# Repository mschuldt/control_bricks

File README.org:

Control Bricks

A collection of composable PCBs for building simple automation solutions.

Bricks are connected in sequence, each performing a simple function before
passing control to the next brick. 
Bricks can have sensor inputs, and outputs for actuators.

The goal is to create reliable and maintainable solutions 
without any custom application specific software. 
The PCBs provide buttons and indicators for the control interface. 
Each output has buttons for manual activation for testing and debugging.

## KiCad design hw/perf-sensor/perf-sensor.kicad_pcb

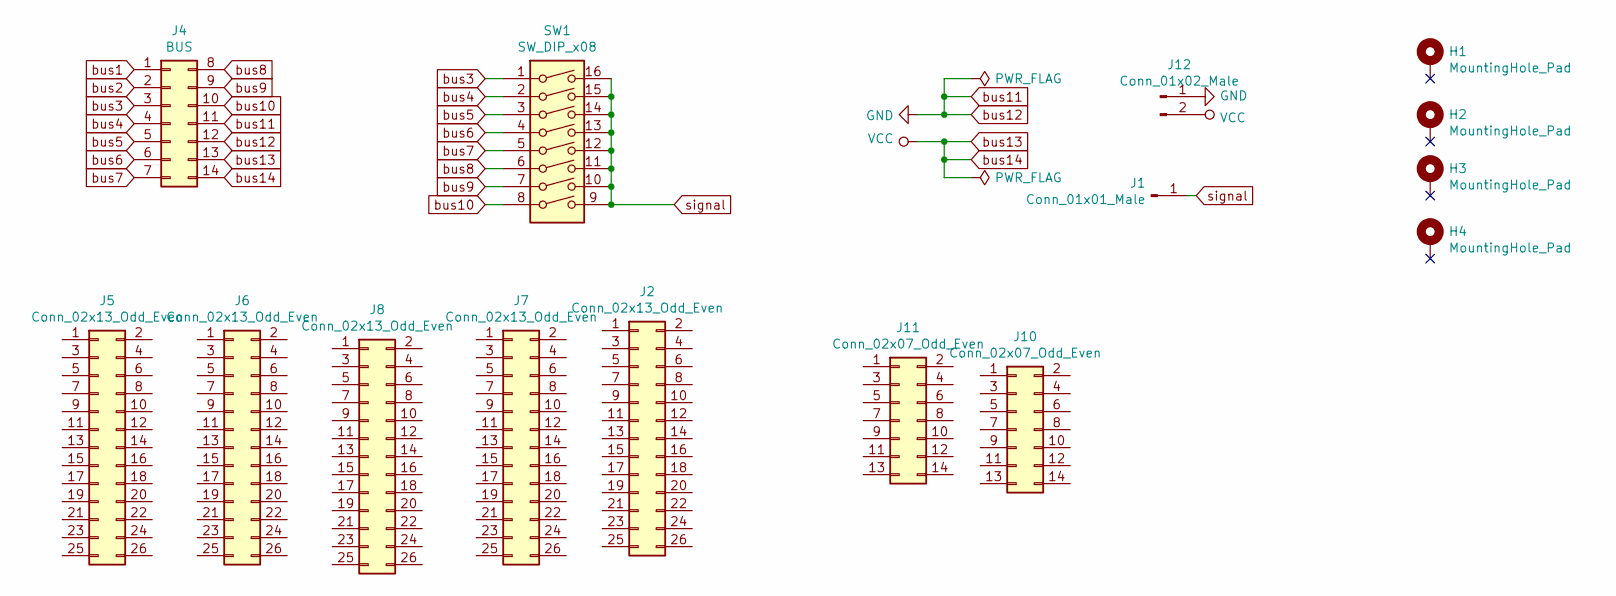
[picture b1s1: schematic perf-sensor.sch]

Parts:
H1, H2, H3, H4: MountingHole_Pad; MountingHole_3.2mm_M3
J1: Conn_01x01_Male; PinHeader_1x01_P2.54mm_Vertical
J2, J5, J6, J7, J8: Conn_02x13_Odd_Even; PinHeader_2x13_P2.54mm_Vertical
J4: BUS; PinHeader_2x07_P2.54mm_Vertical
J10, J11: Conn_02x07_Odd_Even; PinHeader_2x07_P2.54mm_Vertical
J12: Conn_01x02_Male; PinHeader_1x02_P2.54mm_Vertical
SW1: SW_DIP_x08; DIP-16_W7.62mm_SMDSocket_SmallPads

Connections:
bus1: J4.1
bus2: J4.2
bus3: J4.3, SW1.1
bus4: J4.4, SW1.2
bus5: J4.5, SW1.3
bus6: J4.6, SW1.4
bus7: J4.7, SW1.5
bus8: J4.8, SW1.6
bus9: J4.9, SW1.7
bus10: J4.10, SW1.8
bus11: J4.11, J4.12, J12.1
bus13: J4.13, J4.14, J12.2
signal: J1.1, SW1.9, SW1.10, SW1.11, SW1.12, SW1.13, SW1.14, SW1.15, SW1.16

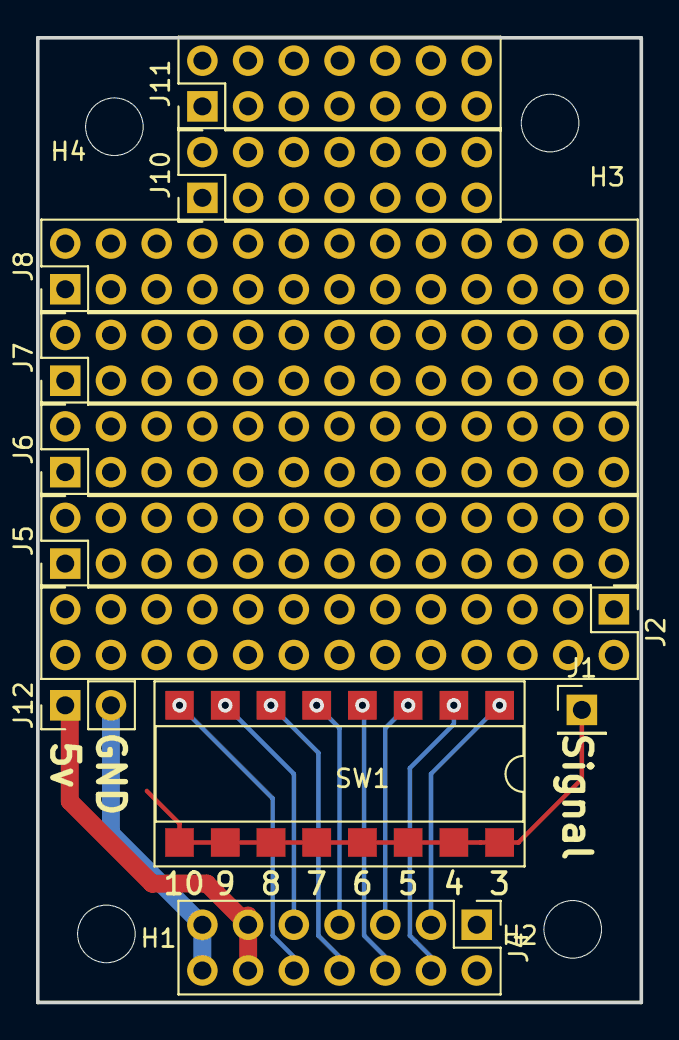
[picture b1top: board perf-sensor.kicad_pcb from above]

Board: 2 copper layers, 33.5 x 53.6 mm, 15 parts (0 on the bottom side), 11 nets.

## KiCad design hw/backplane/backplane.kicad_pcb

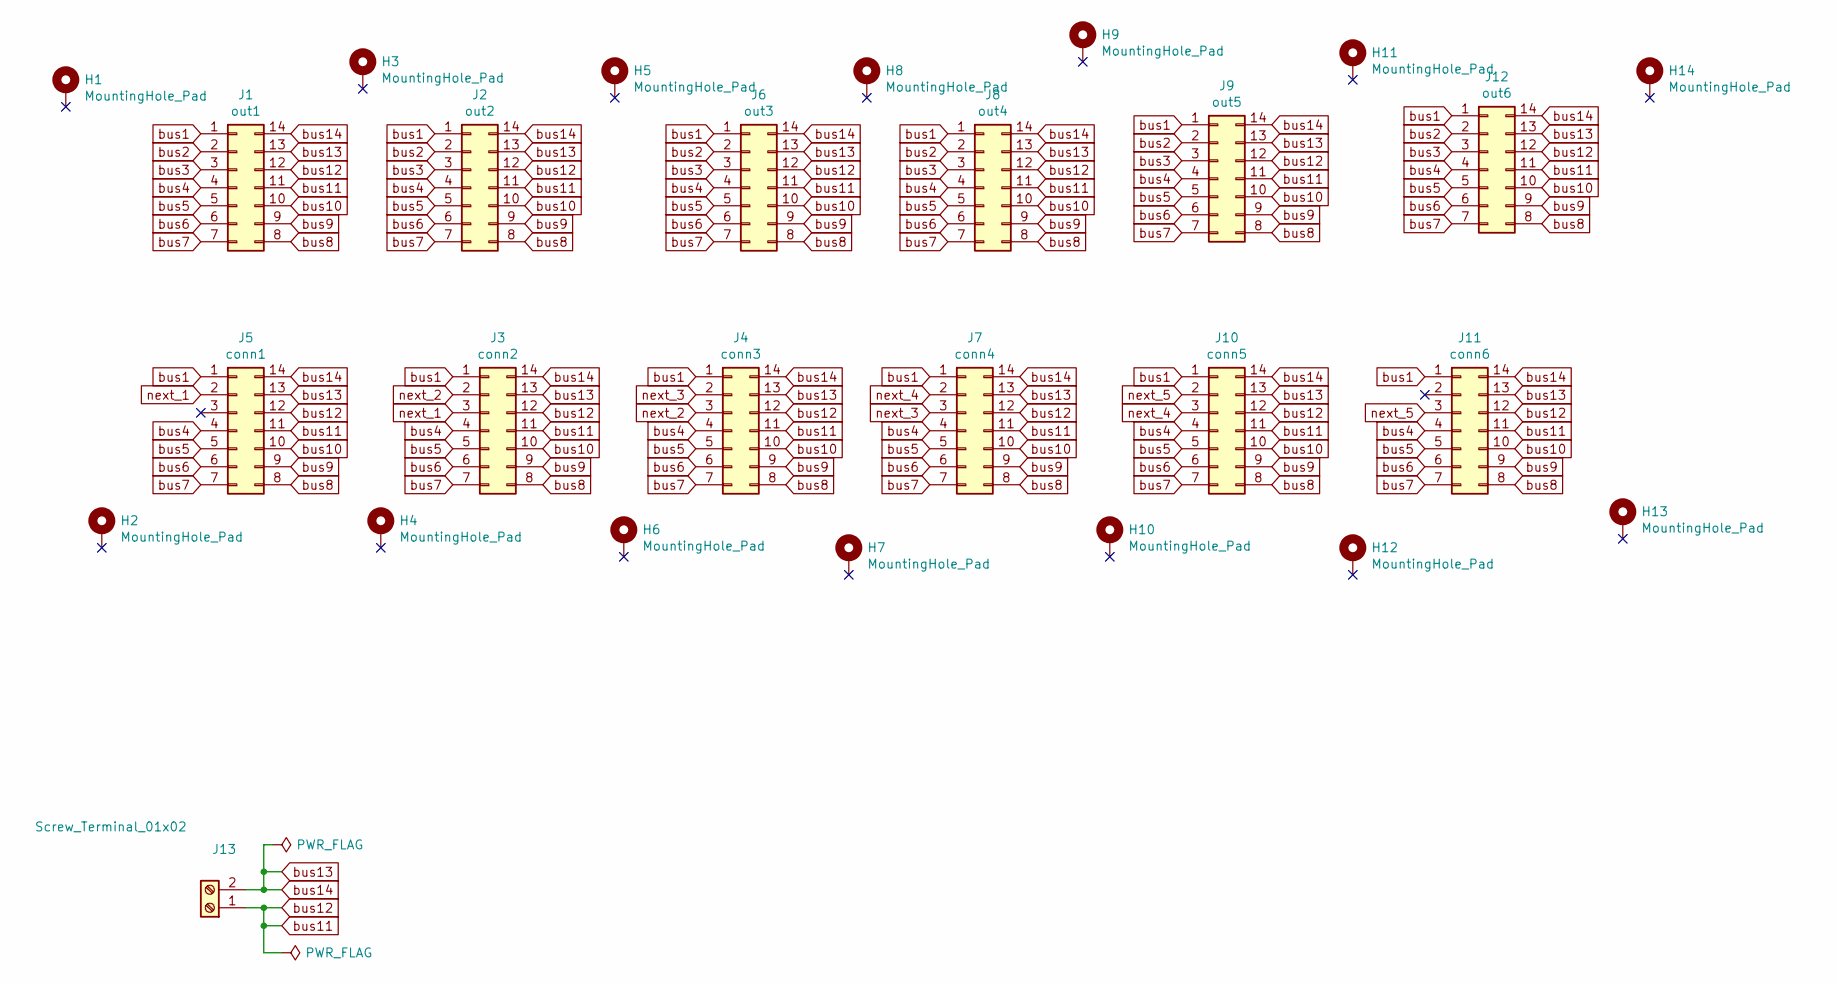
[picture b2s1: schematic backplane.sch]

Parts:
H1, H2, H3, H4, H5, H6, H7, H8, H9, H10, H11, H12, H13, H14: MountingHole_Pad; MountingHole_3.2mm_M3_Pad
J1: out1; PinHeader_2x07_P2.54mm_Vertical
J2: out2; PinHeader_2x07_P2.54mm_Vertical
J3: conn2; PinHeader_2x07_P2.54mm_Vertical
J4: conn3; PinHeader_2x07_P2.54mm_Vertical
J5: conn1; PinHeader_2x07_P2.54mm_Vertical
J6: out3; PinHeader_2x07_P2.54mm_Vertical
J7: conn4; PinHeader_2x07_P2.54mm_Vertical
J8: out4; PinHeader_2x07_P2.54mm_Vertical
J9: out5; PinHeader_2x07_P2.54mm_Vertical
J10: conn5; PinHeader_2x07_P2.54mm_Vertical
J11: conn6; PinHeader_2x07_P2.54mm_Vertical
J12: out6; PinHeader_2x07_P2.54mm_Vertical
J13: Screw_Terminal_01x02; PinHeader_1x02_P2.54mm_Vertical

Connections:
bus1: J1.1, J2.1, J3.1, J4.1, J5.1, J6.1, J7.1, J8.1, J9.1, J10.1, J11.1, J12.1
bus2: J1.2, J2.2, J6.2, J8.2, J9.2, J12.2
bus3: J1.3, J2.3, J6.3, J8.3, J9.3, J12.3
bus4: J1.4, J2.4, J3.4, J4.4, J5.4, J6.4, J7.4, J8.4, J9.4, J10.4, J11.4, J12.4
bus5: J1.5, J2.5, J3.5, J4.5, J5.5, J6.5, J7.5, J8.5, J9.5, J10.5, J11.5, J12.5
bus6: J1.6, J2.6, J3.6, J4.6, J5.6, J6.6, J7.6, J8.6, J9.6, J10.6, J11.6, J12.6
bus7: J1.7, J2.7, J3.7, J4.7, J5.7, J6.7, J7.7, J8.7, J9.7, J10.7, J11.7, J12.7
bus8: J1.8, J2.8, J3.8, J4.8, J5.8, J6.8, J7.8, J8.8, J9.8, J10.8, J11.8, J12.8
bus9: J1.9, J2.9, J3.9, J4.9, J5.9, J6.9, J7.9, J8.9, J9.9, J10.9, J11.9, J12.9
bus10: J1.10, J2.10, J3.10, J4.10, J5.10, J6.10, J7.10, J8.10, J9.10, J10.10, J11.10, J12.10
bus11: J1.11, J1.12, J2.11, J2.12, J3.11, J3.12, J4.11, J4.12, J5.11, J5.12, J6.11, J6.12, J7.11, J7.12, J8.11, J8.12, J9.11, J9.12, J10.11, J10.12, J11.11, J11.12, J12.11, J12.12, J13.1
bus13: J1.13, J1.14, J2.13, J2.14, J3.13, J3.14, J4.13, J4.14, J5.13, J5.14, J6.13, J6.14, J7.13, J7.14, J8.13, J8.14, J9.13, J9.14, J10.13, J10.14, J11.13, J11.14, J12.13, J12.14, J13.2
next_1: J3.3, J5.2
next_2: J3.2, J4.3
next_3: J4.2, J7.3
next_4: J7.2, J10.3
next_5: J10.2, J11.3

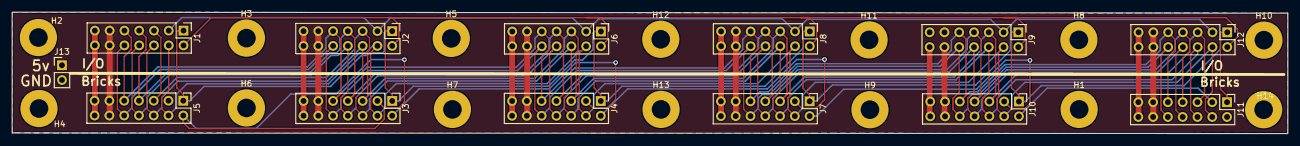
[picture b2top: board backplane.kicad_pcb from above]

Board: 2 copper layers, 219.2 x 20.9 mm, 27 parts (0 on the bottom side), 17 nets.

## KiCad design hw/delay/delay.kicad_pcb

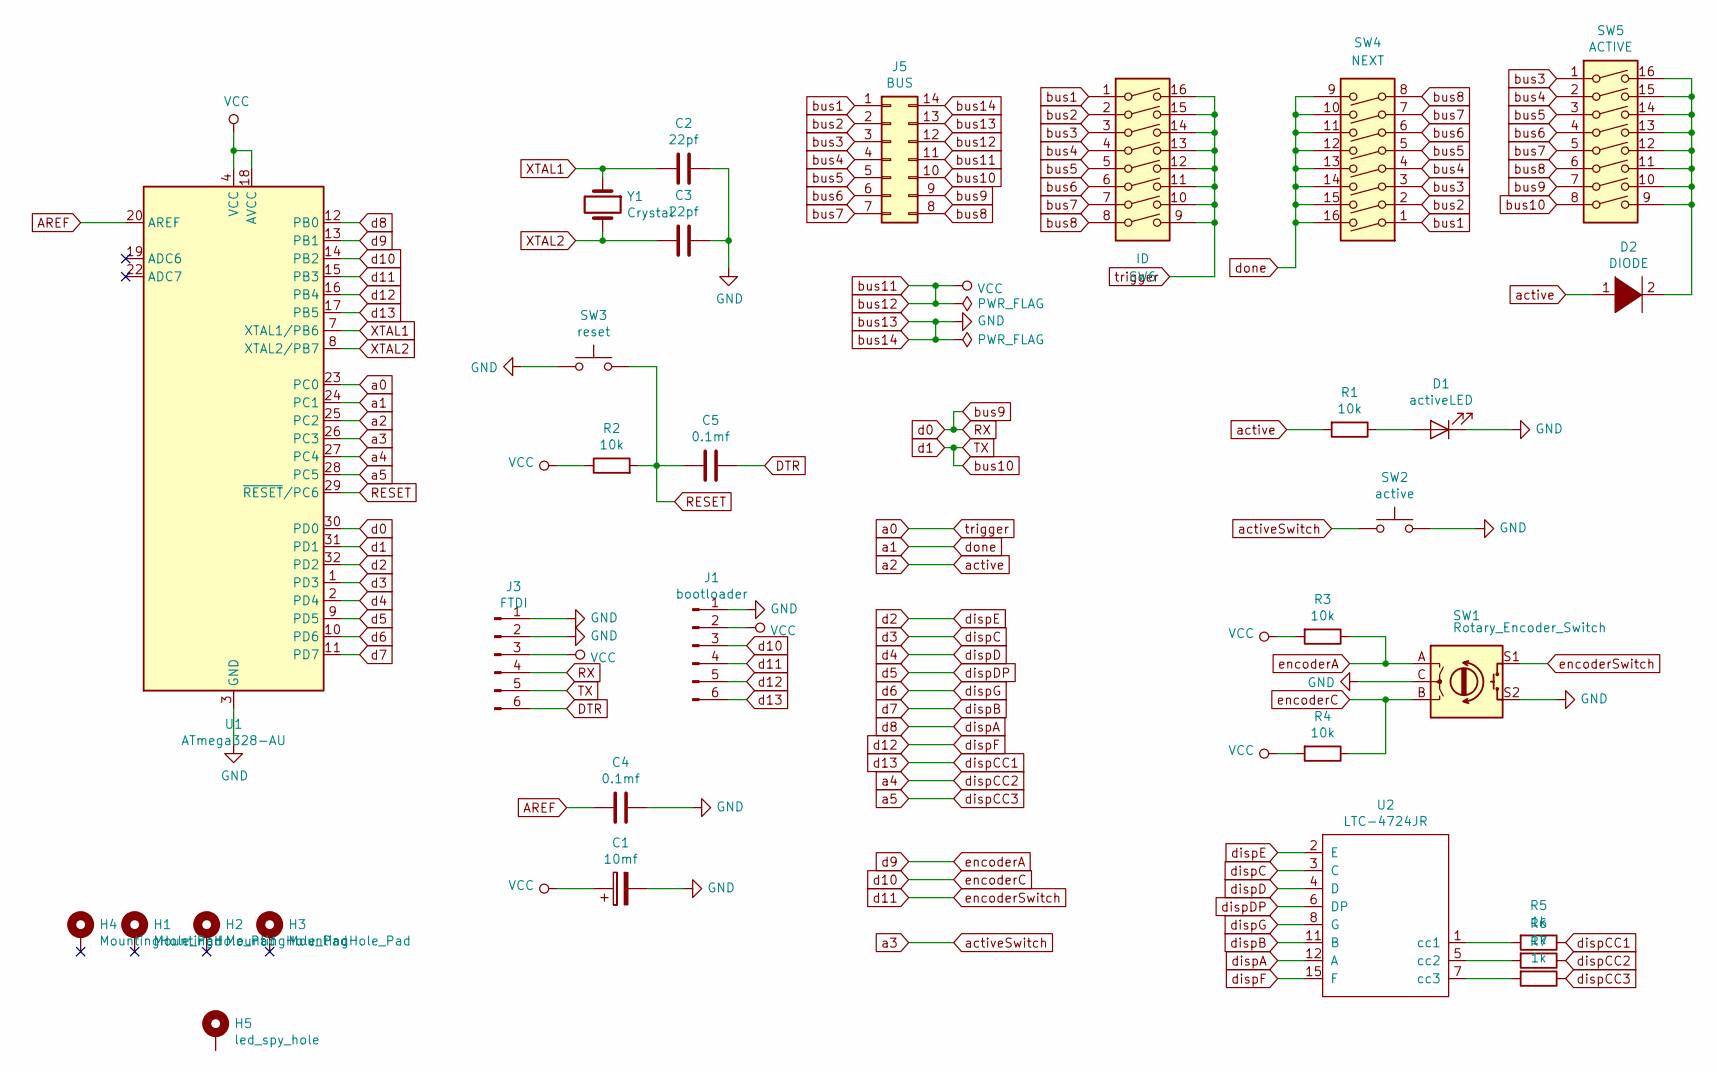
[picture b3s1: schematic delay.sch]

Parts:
C1: 10mf; C_0603_1608Metric
C2, C3: 22pf; C_0603_1608Metric
C4, C5: 0.1mf; C_0603_1608Metric
D1: activeLED; LED_D5.0mm
D2: DIODE; D_0603_1608Metric
H1, H2, H3, H4: MountingHole_Pad; MountingHole_3.2mm_M3_Pad
H5: led_spy_hole; MountingHole_3.2mm_M3
J1: bootloader; edge_connector_3
J3: FTDI; edge_connector_3
J5: BUS; PinHeader_2x07_P2.54mm_Vertical
R1, R2, R3, R4: 10k; R_0603_1608Metric
R5, R6, R7: 1k; R_0603_1608Metric
SW1: Rotary_Encoder_Switch; RotaryEncoder_Alps_EC11E-Switch_Vertical_H20mm_CircularMoun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
SW2: active; SW_SPST_TL3305C
SW3: reset; SW_SPST_TL3305C
SW4: NEXT; DIP-16_W7.62mm_SMDSocket_SmallPads
SW5: ACTIVE; DIP-16_W7.62mm_SMDSocket_SmallPads
SW6: ID; DIP-16_W7.62mm_SMDSocket_SmallPads
U1: ATmega328-AU; TQFP-32_7x7mm_P0.8mm
U2: LTC-4724JR
Y1: Crystal; Crystal_SMD_HC49-SD

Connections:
AREF: C4.1, U1.20 (AREF)
DTR: C5.2, J3.6
unnamed: D1.2 (A), R1.1
unnamed: D2.2 (A), SW5.9, SW5.10, SW5.11, SW5.12, SW5.13, SW5.14, SW5.15, SW5.16
unnamed: R5.2, U2.1 (cc1)
unnamed: R6.2, U2.5 (cc2)
unnamed: R7.2, U2.7 (cc3)
RESET: C5.1, R2.2, SW3.2, U1.29 (~RESET~/PC6)
RX: J3.4, J5.9, SW5.7, U1.30 (PD0)
TX: J3.5, J5.10, SW5.8, U1.31 (PD1)
XTAL1: C2.2, U1.7 (XTAL1/PB6), Y1.1
XTAL2: C3.2, U1.8 (XTAL2/PB7), Y1.2
a0: SW6.9, SW6.10, SW6.11, SW6.12, SW6.13, SW6.14, SW6.15, SW6.16, U1.23 (PC0)
a1: SW4.9, SW4.10, SW4.11, SW4.12, SW4.13, SW4.14, SW4.15, SW4.16, U1.24 (PC1)
a2: D2.1 (K), R1.2, U1.25 (PC2)
a3: SW2.1, U1.26 (PC3)
a4: R6.1, U1.27 (PC4)
a5: R7.1, U1.28 (PC5)
bus1: J5.1, SW4.1, SW6.1
bus2: J5.2, SW4.2, SW6.2
bus3: J5.3, SW4.3, SW5.1, SW6.3
bus4: J5.4, SW4.4, SW5.2, SW6.4
bus5: J5.5, SW4.5, SW5.3, SW6.5
bus6: J5.6, SW4.6, SW5.4, SW6.6
bus7: J5.7, SW4.7, SW5.5, SW6.7
bus8: J5.8, SW4.8, SW5.6, SW6.8
bus11: C1.1, J1.2, J3.3, J5.11, J5.12, R2.1, R3.2, R4.2, U1.4 (VCC), U1.6 (VCC), U1.18 (AVCC)
bus13: C1.2, C2.1, C3.1, C4.2, D1.1 (K), J1.1, J3.1, J3.2, J5.13, J5.14, SW1.C, SW1.S2, SW2.2, SW3.1, U1.3 (GND), U1.5 (GND), U1.21 (GND)
d2: U1.32 (PD2), U2.2 (E)
d3: U1.1 (PD3), U2.3 (C)
d4: U1.2 (PD4), U2.4 (D)
d5: U1.9 (PD5), U2.6 (DP)
d6: U1.10 (PD6), U2.8 (G)
d7: U1.11 (PD7), U2.11 (B)
d8: U1.12 (PB0), U2.12 (A)
d9: R3.1, SW1.A, U1.13 (PB1)
d10: J1.3, R4.1, SW1.B, U1.14 (PB2)
d11: J1.4, SW1.S1, U1.15 (PB3)
d12: J1.5, U1.16 (PB4), U2.15 (F)
d13: J1.6, R5.1, U1.17 (PB5)

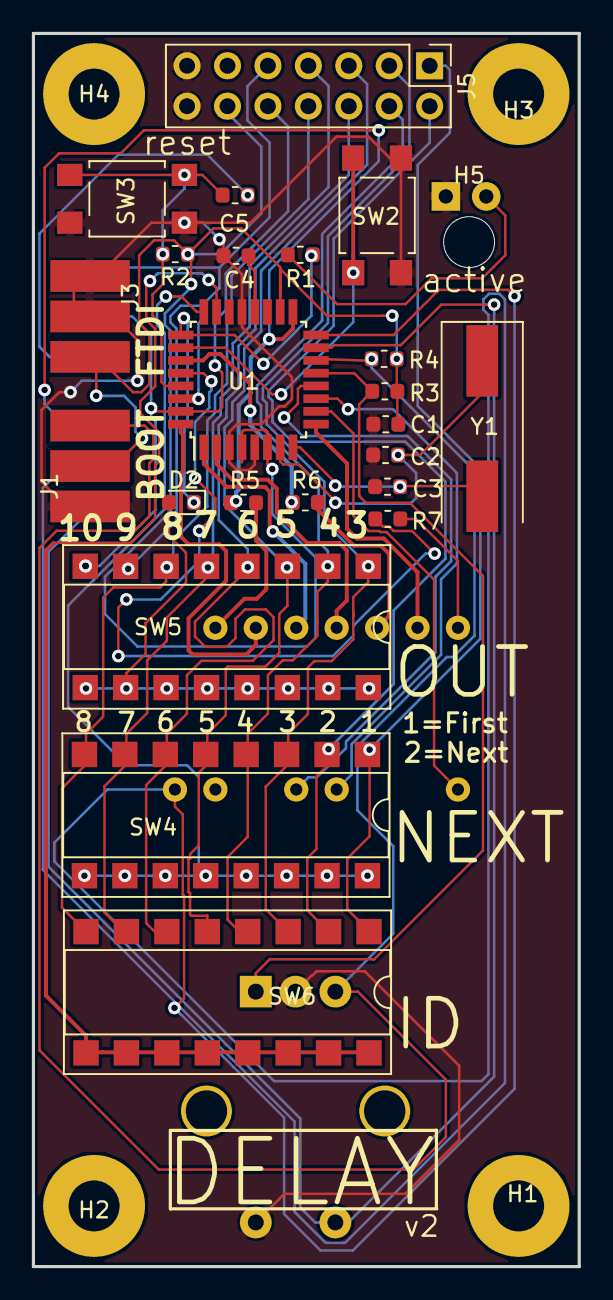
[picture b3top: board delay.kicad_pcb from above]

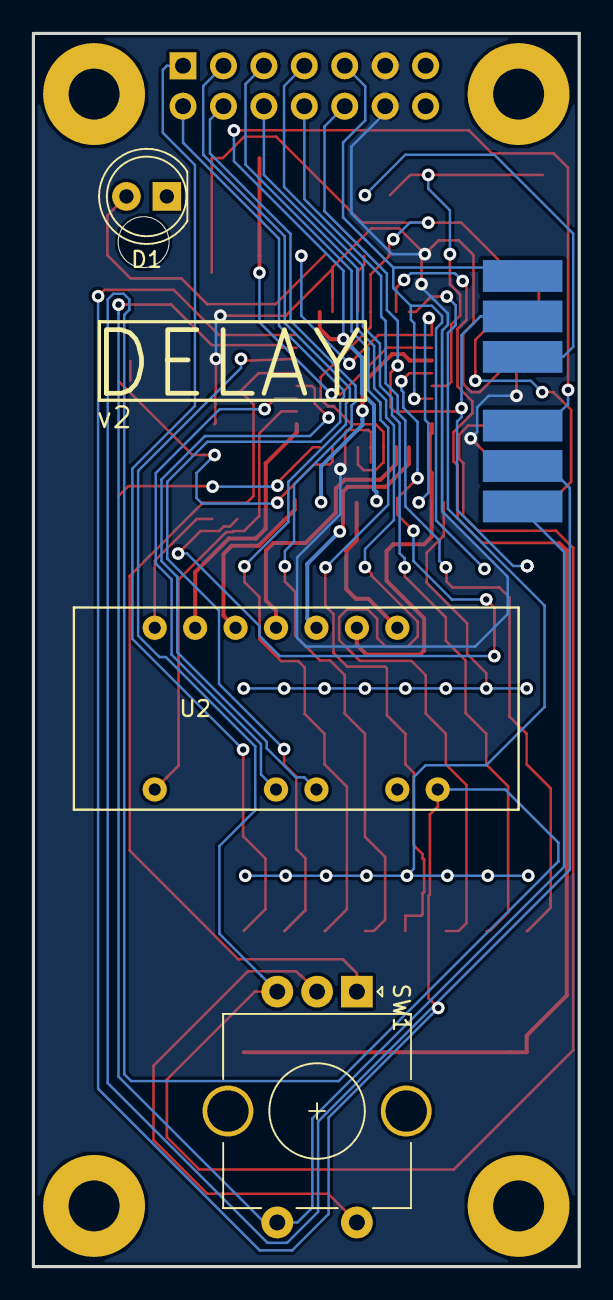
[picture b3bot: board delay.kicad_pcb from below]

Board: 2 copper layers, 34.3 x 77.5 mm, 31 parts (3 on the bottom side), 40 nets.

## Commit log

2018-11-02 initial
2018-11-02 update hardware
2018-11-21 DELAY block v2
2018-11-21 WHILE block v2
2018-11-21 COUNT block v2
2018-11-21 RUN block v2
2018-11-22 backplane
2018-11-23 update backplane
2018-11-23 fix DELAY bus assigments
2018-11-23 fix WHILE bus assignemnts
2018-11-23 fix COUNT bus assigments
2018-11-23 fix RUN bus assigments
2018-11-23 RELAY bus connection
2018-11-24 perf sensor
2018-12-14 relay layout changes
2018-12-15 ignore .zip files
2018-12-15 single zip-gerbers script
2018-12-17 update DELAY block files
